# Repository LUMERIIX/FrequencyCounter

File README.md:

# FrequencyCounter - The most powerfull DIY FrequnecyCounter
## Introduction
FrequencyCounter is a soft- and hardware project which is a FPGA based FrequencyCounter. The FrequencyCounter is controlled by an GUI Interface ([SigrokLcd](https://github.com/LUMERIIX/SigrokLcd) )on the usb connected Host-PC. A single USB cable for Data and Power supply keeps the construction simple and clean as possible. The GUI is custom-made for this project behind the GUI runs [Sigrok](https://sigrok.org/) a open-source tool for controlling measure devices like frequency counters, multimeters, oscilloscopes etc. The project aims to be a simple, cheap, useful and accurate measure device for everyone. The layout is made in [KiCad]( http://kicad.org/) a open-source layout tool. The Project is open and everyone is wellcome to work on this project and contribute his extensions and improvements.

## Concept
Comming Soon!

## Hardware
The Hardware is based on a Spartan 6 FPGA which is the heartpiece of the entire circuit. The circuit is reduced to its minimal. The PCB ist a four-layer 1.6mm thick FR4 Board which makes it more expensive but the layout is much cleaner and the signal quality can be increased. The PCB has mounted components on top and bottom site of it. The Mounting on the bottom site is reduced to the minimal to keep it simple an allows also the use without a hosing.<br> 

### Housing
I created a simple and clean plexiglas housing for the PCB which fits the style of the prject very well. The design of the housing is inspired by the [Sick of Beige](http://dangerousprototypes.com/docs/Sick_of_Beige_compatible_cases) cases.<br> 

### Internal Clock Reference
The mouting of the Circuit give you the choice to mout the expensive **OCXO**(Oven Controlled Oscillator) or the way cheaper **VCTCXO**(Voltage Controller Temperatur Compensated Oscillator). In fact of this the precicion of the tool is scalable but I recommend you to mount the cheaper option because the difference in the accuracy is not as much as the price difference. <br>

### Input Circuits
The Input Circuits of each channel are different because not one of them fit in all usage situations.<br> 
The input circuit of **CHA** is realized with an voltage limiter and a HP-Filter at the inlet, followed by a divider (/8) with a HP-Filter and a voltage divider at the output to change the bias point. The change of the bias point is neccessary for the fpga to allow the signal detection.<br>
The most complex incput circuit is the one of the **external reference** (Ext.Ref). The circuit is out of the LTC6957 Datasheet and is often used for reference clocks. The transformator at the inlet make it impossible to use this circuit for both other channels of the FrequencyCounter (frequnecy reasons).<br>
**Channel B** is simpler than the other input ciruits. After the inlet it follows a voltage limiter and a very-fast comparator for edge detecting.<br>
### Communication
The Communication of the Device is over USB/UART through this its possible to have only one cable for programming, powersupply and also communication. On the PCB of the Counter a FTDI (FT2232) is mounted. Through this chip it's possible to programm the FPGA with JTAG and also have a USART Bus to the FPGA for the communication and the data. The Protocol which is used for the controlling consits only out of one command-byte which controls the hole device. The Commands you see in the Command Overview.<br>
**Command Overview**<br><br>
<br><br>
**Communication Overview**<br><br>
<br>

### Hardware Overview:<br>
<br>

## Software
### VHDL
**UART**<br>
The UART component isn't self written it is a adjusted version of the [UART component of Scott Larson](https://eewiki.net/pages/viewpage.action?pageId=59507062) of the eewiki. The component was extended by a Wishbone Interface to fit the projects architecture. The UART interface is used for the communication with the host-pc.<br><br>
**I2C**<br>
The I2C Master Component is also not self written it's base is from [opencores](https://opencores.org/project,i2c?do=projects&download=i2c). The component works fine and it's a big advantage to have a originally wishbone interface included. I2C is in the FrequnecyCounter used to control the DAC wich provides to control voltage for the oscillators.<br><br>
**ZPU**<br>
The [ZPU](https://github.com/zylin/zpu) is a open-source VHDL project from github wich includes a small 32bit CPU. The base ZPU Repo consist of different cores and testbenches but is very confusing. In fact of this I created a fork of the repo and set up a [working base](https://github.com/LUMERIIX/zpu) for the FrequencyCounter Project.<br><br>
**FrequencyCounter**<br>
The FrequencyCounter VHDL Code is the main part which counts our signals. The FrequencyCounter includes a ChannelSelctor which connect the desired Channels to the Counter itself. Furthermore the component includes a GateTimeGenerator which open a Countergate for a selected duration of time. The Signals are counted simultaneously with two identical VHDL counters. Each counter counts the amout of signal periods in this GateTime. Through the knowledge of the constant reference and the countervalue of the Reference Clock we can calculate the frequency of the unknown signal. This kind of Counter is called [Recirprocal Counter](https://en.wikipedia.org/wiki/Frequency_counter).<br><br>
**Procedure & Calculation**<br><br>
<br><br>

<br><br><br><br><br><br><br><br><br><br>

**VHDL Abstraction**<br><br>
<br><br>
**VHDL FrequencyCounter Abstraction**<br><br>
<br>
### C-Code
The C-Code is the Programm Code for the implemented VHDL CPU [ZPU](https://github.com/zylin/zpu) or a so called [SOC](https://en.wikipedia.org/wiki/System_on_a_chip)(System-on-a-Chip). The C-Code implements the Protocol for the communication over uart and i2c. The ZPU also controls the entire VHDL Components and handles the data. The Code is obviously written in C and is based on a state-machine. The C-Code is converted in a dualported-RAM (VHDL Component) which is located in the VHDL Project and is connected to the Wishbone-Bus of the ZPU. 

## Download & Installation
**It's recommended to use a Linux Host-PC the project is tested and developt on Fedora 27 so I recommend to install a Fedora VM in VMWare Worksation**

```
cd
gedit .bashrc
```
Add following lines:
```
export PKG_CONFIG_PATH=/usr/local/lib/pkgconfig/ 
export PYTHONPATH=/usr/local/lib64/python2.7/site-packages/
```
Save and Close gedit.<br>
Install dependencies:
```
sudo dnf install gcc-gfortran apr-devel apr-util-devel octave*
sudo dnf install gcc-c++
sudo dnf update
sudo dnf upgrade
sudo svn git cppunit-devel rabbitvcs*
sudo dnf copr enable jenslody/codeblocks
sudo dnf install codeblocks codeblocks-contrib
sudo dnf install libftdi-devel libusb-devel xterm
sudo dnf install automake libtool autoconf make cmake autoconf-archive pkgconfig glib2-devel libzip-devel check-devel doxygen
sudo dnf install glibmm24-devel python-devel numpy pygobject3-devel swig
sudo dnf install redhat-rpm-config python3-devel qt5 qt5-devel boost-devel
```
Next Install libserialport and the adjusted version of libsigrok:
```
git clone git://sigrok.org/libserialport
cd /libserialport
./autogen.sh 
./configure
make
sudo make install

git clone https://github.com/LUMERIIX/libsigrok_FreqCount
cd libsigrok_FreqCount
./autogen.sh
PKG_CONFIG_PATH=/usr/local/lib/pkgconfig/ ./configure 
make -j4
sudo PKG_CONFIG_PATH=/usr/local/lib/pkgconfig/ PYTHONPATH=/usr/local/lib64/python2.7/site-packages/ make install
sudo ldconfig /usr/local/lib
```
Download the FrequencyCounter Repo:
```
git clone https://github.com/LUMERIIX/FrequencyCounter
cd FrequencyCounter 
```
**Optional** Download the fork of the ZPU Repo to have all source files 
```
cd
git clone https://github.com/LUMERIIX/zpu
```
The source files are located under
```
cd zpu/zpu/hdl/zpu4
```
Next Install openocd for flashing the bitstream:
```
sudo dnf install git libtool autoconf texinfo libusb-dev
sudo dnf install libftdi
cd
git clone git://git.code.sf.net/p/openocd/code openocd
cd ~/openocd
./bootstrap
./configure --enable-maintainer-mode --disable-werror --enable-ftdi
make
sudo make install
```
Create Directory for Config files of Openocd
```
cd ~
mkdir openocd-bin
cd ~/openocd/tcl
cp -r * ~/openocd-bin
cd ../src
cp openocd ~/openocd-bin
```
Add the Interface Config file for the FT2232
```
cd 
cp FrequnecyCounter/FTDI/ft2232-jtag.cfg openocd-bin/interface/ftdi
```
Download [SigrokLcd](https://github.com/LUMERIIX/SigrokLcd) or [SigrokCLI](https://sigrok.org/wiki/Linux)

### Set up the FTDI Chip (FT2232d)
First download [FT_PROG](http://www.ftdichip.com/Support/Utilities.htm#FT_PROG) and install it on your Host-pc.<br>
Open FT_PROG and Load FrequencyCounter.xml Template from directrory /FrequnceyCounter/Documentation/FrequencyCounter_Template.xml<br>
Connect your FrequencyCounter via USB to the Host-PC and power it!<br>
**Check first the Voltages of the Powersupply on the PCB to make sure the circuit is working correctly!**<br>
Scan for Devices (Devices --> Scan&Parse)<br>
A Device with Chip Type: FT2232D should be listed in the Device Tree on the left.<br>
Program Template on FTDI Chip (Devices --> Program)<br>
Now your FTDI Chip should be set-up correctly
Else take a look in the [FT_PROG manual](http://www.ftdichip.com/Support/Documents/AppNotes/AN_124_User_Guide_For_FT_PROG.pdf)

## How to use it
The actual bitstream you find under /bitstream:
```
cd
cd FrequencyCounter/bitstream
```
To flash the bitstream move to the openocd directory
```
cd
cd openocd
mdkdir bitstream
cp ../FrequencyCounter/bitstream/frequencycountertop.bit bitstream
```
Flash Command
```
openocd -f interface/ftdi/ft2232-jtag.cfg -f cpld/xilinx-xc6s.cfg -c "init; xc6s_program xc6s.tap; pld load 0 bitstream/frequnecycountertop.bit; exit"
```
**If a error is thrown try it as root.
And change write permission of the USB port where the Hardware is connected and try again!**

Open SigrokLcd and try to get some Data
```
cd
cd SigrokLcd/bin/Release
./SigrokLcd
```
If the GUI doesn't exit and you can finish the configuration of the connection in SigrokLcd you handled the bigest step. 
The Preset for the ChannelSelect is on CHA so you should receive a Frequency of quite a feq MHz. This Frequency exists through the output voltage swing of the frequency divider.<br>
**Congrats it seems that your DIY FrequencyCounter works!**

### Contact
If you have a Problem, a improvment or need Information don't hesitate to contact me.<br>
email: lukas.jenni@hotmail.de

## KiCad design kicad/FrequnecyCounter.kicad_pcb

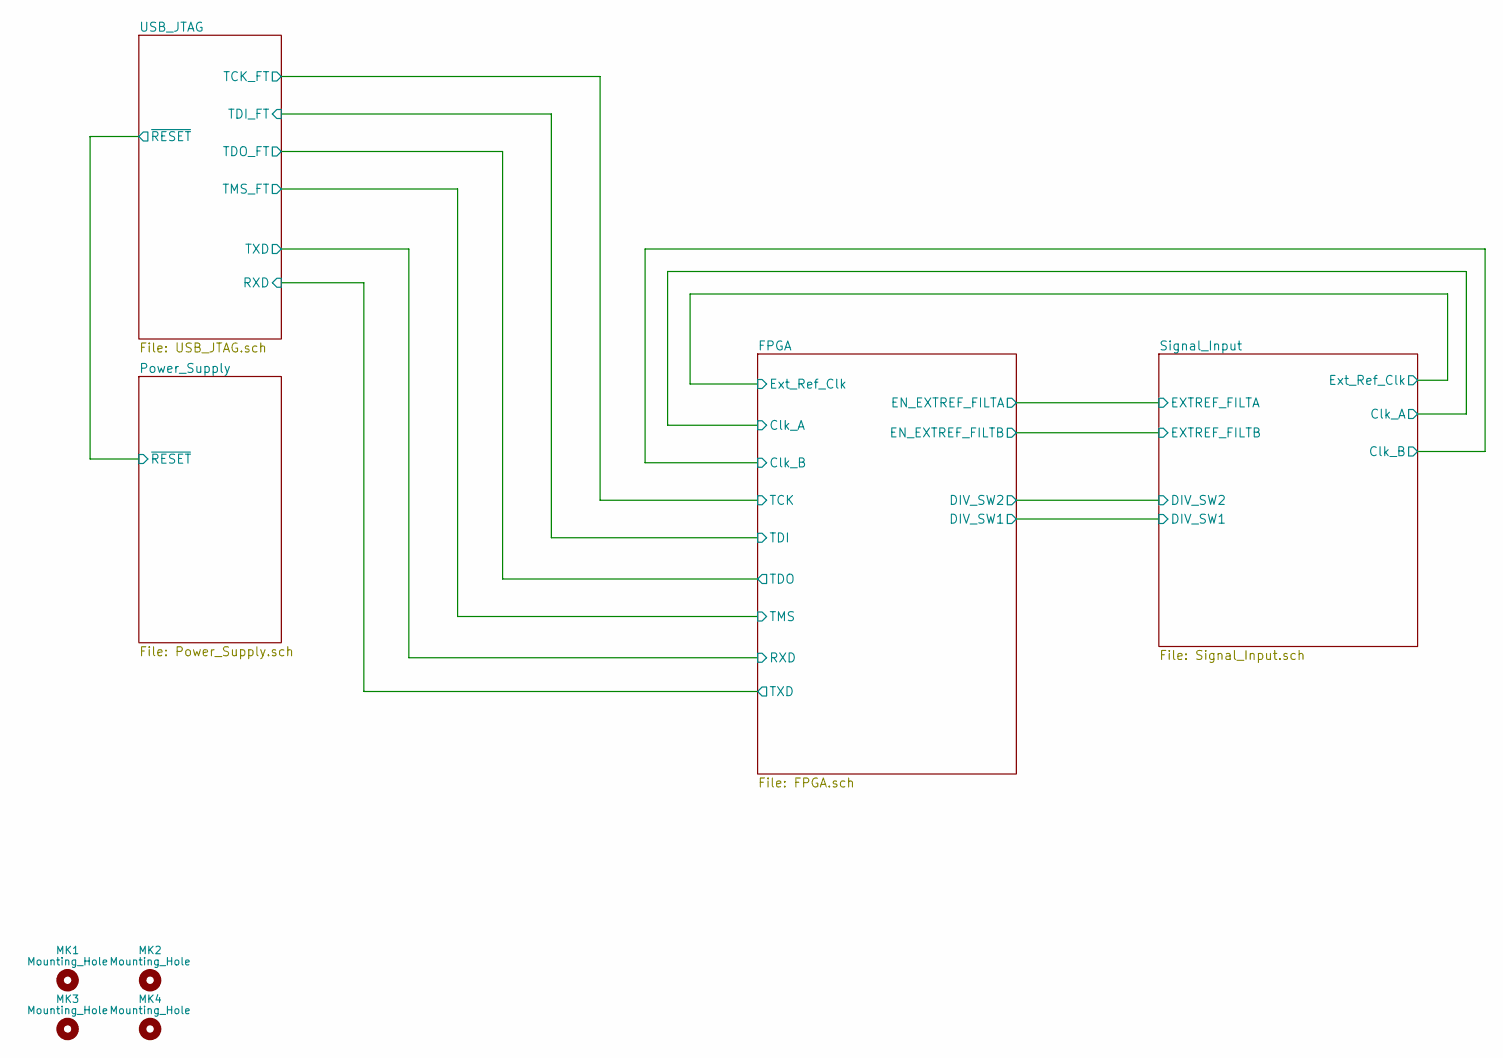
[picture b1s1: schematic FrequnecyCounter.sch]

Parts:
MK1, MK2, MK3, MK4: Mounting_Hole; MountingHole_3.2mm_M3_ISO7380

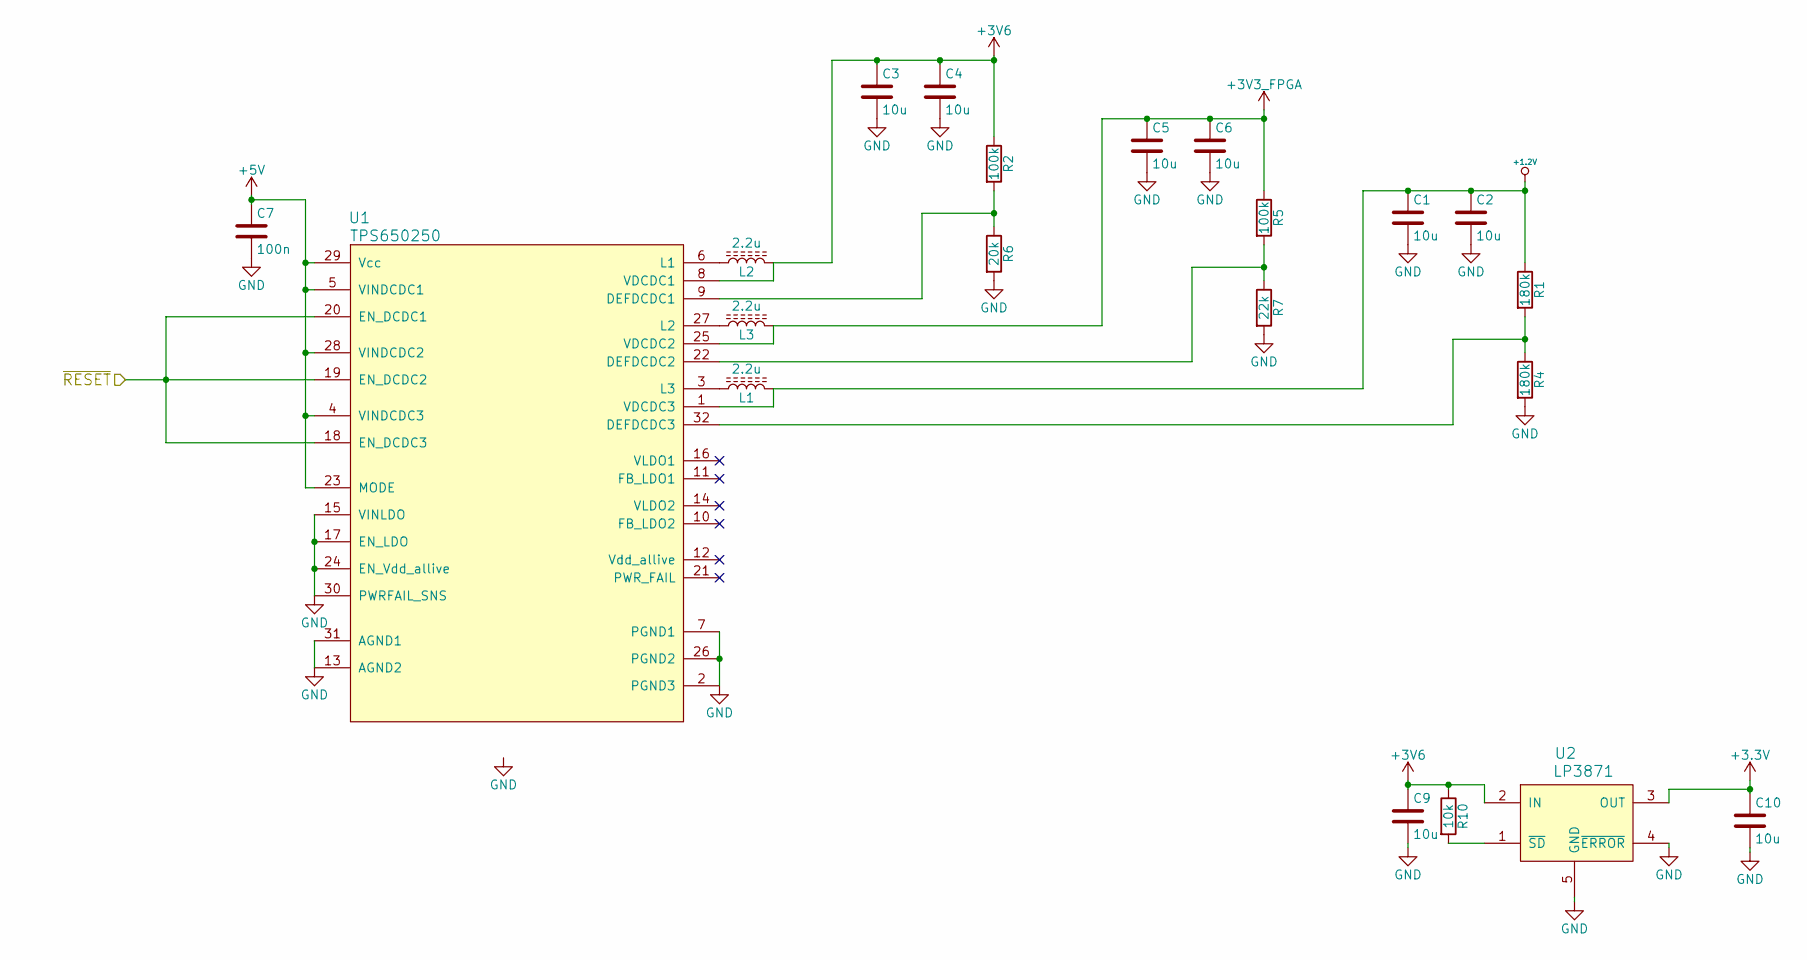
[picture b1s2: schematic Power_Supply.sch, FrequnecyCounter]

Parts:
C1, C2, C3, C4, C5, C6, C9, C10: 10u; Cap_0603_HandSoldering_1
C7: 100n; Cap_0603_HandSoldering_1
L1, L2, L3: 2.2u; LPS5030
R1, R4: 180k; R_0603_HandSoldering
R2, R5: 100k; R_0603_HandSoldering
R6: 20k; R_0603_HandSoldering
R7: 22k; R_0603_HandSoldering
R10: 10k; R_0603_HandSoldering
U1: TPS650250; QFN-32-1EP_5x5mm_Pitch0.5mm
U2: LP3871; SOT-223-5

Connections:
+1.2V: C1.1, C2.1, L1.2, R1.1, U1.1 (VDCDC3); also elsewhere on the board
+3V3_FPGA: C5.1, C6.1, L3.2, R5.1, U1.25 (VDCDC2); also elsewhere on the board
+3V6: C3.1, C4.1, C9.1, L2.2, R2.1, R10.1, U1.8 (VDCDC1), U2.2 (IN)
+5V: C7.1, U1.4 (VINDCDC3), U1.5 (VINDCDC1), U1.23 (MODE), U1.28 (VINDCDC2), U1.29 (Vcc); also elsewhere on the board
/Power_Supply/~RESET: U1.18 (EN_DCDC3), U1.19 (EN_DCDC2), U1.20 (EN_DCDC1); also elsewhere on the board
GND: C1.2, C2.2, C3.2, C4.2, C5.2, C6.2, C7.2, C9.2, C10.2, R4.2, R6.2, R7.2, U1.2 (PGND3), U1.7 (PGND1), U1.13 (AGND2), U1.15 (VINLDO), U1.17 (EN_LDO), U1.24 (EN_Vdd_allive), U1.26 (PGND2), U1.30 (PWRFAIL_SNS), U1.31 (AGND1), U1.33 (GND_PANEL), U2.4 (~ERROR), U2.5 (GND); also elsewhere on the board
unnamed: L1.1, U1.3 (L3)
unnamed: L2.1, U1.6 (L1)
unnamed: L3.1, U1.27 (L2)
unnamed: R1.2, R4.1, U1.32 (DEFDCDC3)
unnamed: R2.2, R6.1, U1.9 (DEFDCDC1)
unnamed: R5.2, R7.1, U1.22 (DEFDCDC2)
unnamed: R10.2, U2.1 (~SD)

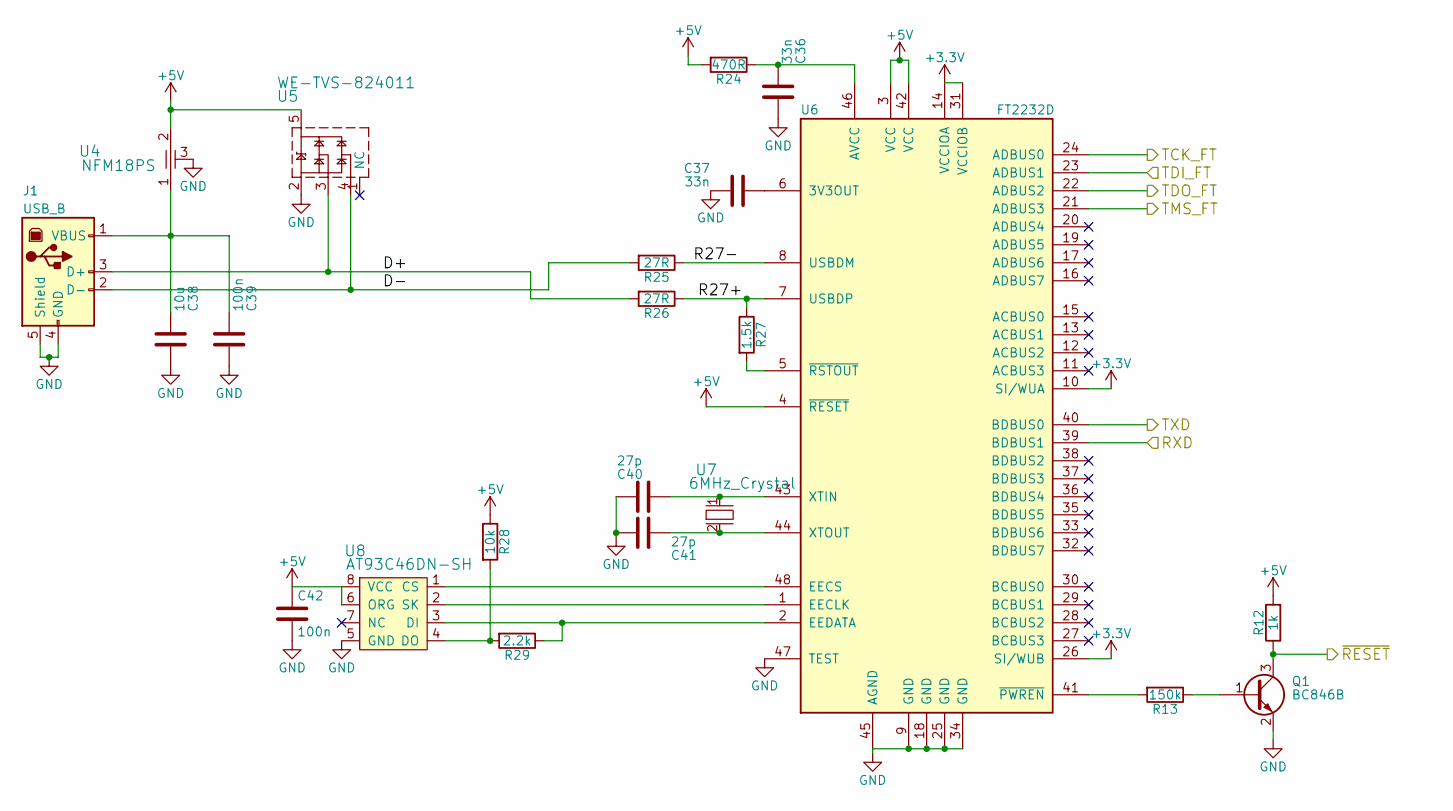
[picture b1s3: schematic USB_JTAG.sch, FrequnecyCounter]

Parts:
C36, C37: 33n; Cap_0603_HandSoldering_1
C38: 10u; Cap_0603_HandSoldering_1
C39, C42: 100n; Cap_0603_HandSoldering_1
C40, C41: 27p; Cap_0603_HandSoldering_1
J1: USB_B; USB_B_liegen_SMD
Q1: BC846B; SOT-23
R12: 1k; R_0603_HandSoldering
R13: 150k; R_0603_HandSoldering
R24: 470R; R_0603_HandSoldering
R25, R26: 27R; R_0603_HandSoldering
R27: 1.5k; R_0603_HandSoldering
R28: 10k; R_0603_HandSoldering
R29: 2.2k; R_0603_HandSoldering
U4: NFM18PS
U5: WE-TVS-824011; SOT-23-5
U6: FT2232D; LQFP-48_7x7mm_Pitch0.5mm
U7: 6MHz_Crystal; Crystal_SMD_HC49-SD
U8: AT93C46DN-SH; SOIC-8_3.9x4.9mm_Pitch1.27mm

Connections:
+5V: C42.1, R12.2, R24.2, R28.1, U4.2, U5.5, U6.3 (VCC), U6.4 (~RESET), U6.42 (VCC), U8.6 (ORG), U8.8 (VCC); also elsewhere on the board
/FPGA/RXD: U6.40 (BDBUS0); also elsewhere on the board
/FPGA/TCK: U6.24 (ADBUS0); also elsewhere on the board
/FPGA/TDI: U6.23 (ADBUS1); also elsewhere on the board
/FPGA/TDO: U6.22 (ADBUS2); also elsewhere on the board
/FPGA/TMS: U6.21 (ADBUS3); also elsewhere on the board
/Power_Supply/~RESET: Q1.3 (C), R12.1; also elsewhere on the board
/USB_JTAG/D+: J1.3 (D+), R26.2, U5.3
/USB_JTAG/D-: J1.2 (D-), R25.2, U5.4
/USB_JTAG/R27+: R26.1, R27.1, U6.7 (USBDP)
/USB_JTAG/R27-: R25.1, U6.8 (USBDM)
/USB_JTAG/RXD: U6.39 (BDBUS1); also elsewhere on the board
GND: C36.2, C37.1, C38.2, C39.2, C40.2, C41.2, C42.2, J1.4 (GND), J1.5 (Shield), Q1.2 (E), U4.3, U5.2, U6.9 (GND), U6.18 (GND), U6.25 (GND), U6.34 (GND), U6.45 (AGND), U6.47 (TEST), U8.5 (GND); also elsewhere on the board
unnamed: C36.1, R24.1, U6.46 (AVCC)
unnamed: C37.2, U6.6 (3V3OUT)
unnamed: C38.1, C39.1, J1.1 (VBUS), U4.1
unnamed: C40.1, U6.43 (XTIN), U7.1
unnamed: C41.1, U6.44 (XTOUT), U7.2
unnamed: Q1.1 (B), R13.1
unnamed: R13.2, U6.41 (~PWREN)
unnamed: R27.2, U6.5 (~RSTOUT)
unnamed: R28.2, R29.2, U8.4 (DO)
unnamed: R29.1, U6.2 (EEDATA), U8.3 (DI)
unnamed: U6.1 (EECLK), U8.2 (SK)
unnamed: U6.48 (EECS), U8.1 (CS)

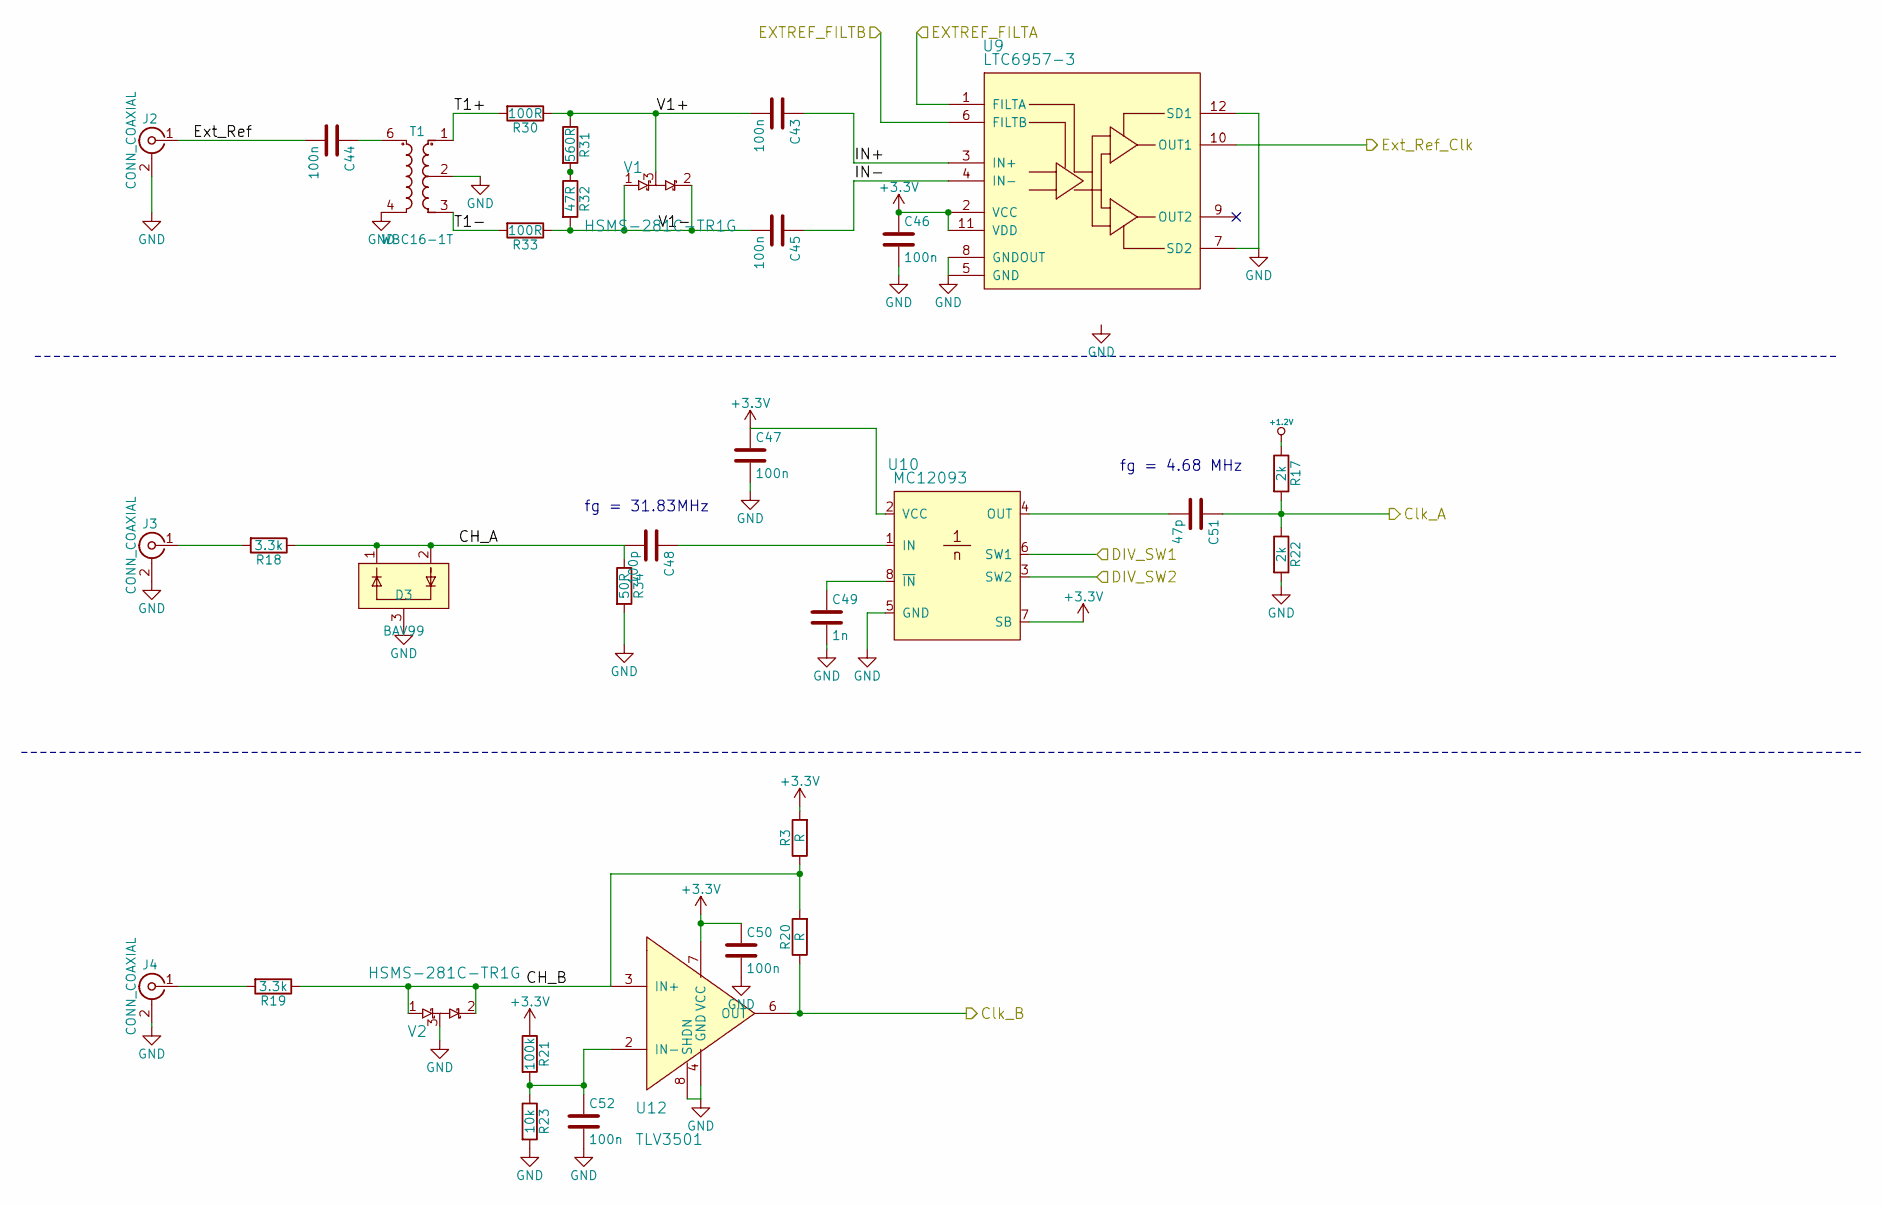
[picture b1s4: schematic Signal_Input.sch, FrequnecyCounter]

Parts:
C43, C44, C45, C46, C47, C50, C52: 100n; Cap_0603_HandSoldering_1
C48: 100p; Cap_0603_HandSoldering_1
C49: 1n; Cap_0603_HandSoldering_1
C51: 47p; Cap_0603_HandSoldering_1
D3: BAV99; SOT-23
J2, J3, J4: CONN_COAXIAL; bncf-horizontal
R3, R20: R; R_0603_HandSoldering
R17, R22: 2k; R_0603_HandSoldering
R18, R19: 3.3k; R_0603_HandSoldering
R21: 100k; R_0603_HandSoldering
R23: 10k; R_0603_HandSoldering
R30, R33: 100R; R_0603_HandSoldering
R31: 560R; R_0603_HandSoldering
R32: 47R; R_0603_HandSoldering
R34: 50R; R_0603_HandSoldering
T1: WBC16-1T; wbc-16-1T
U9: LTC6957-3; DFN-12-1EP_3x3mm_Pitch0.45mm
U10: MC12093; SOIC-8_3.9x4.9mm_Pitch1.27mm
U12: TLV3501; SOIC-8-N
V1, V2: HSMS-281C-TR1G; SOT-323_SC-70_Handsoldering

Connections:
+1.2V: R17.1; also elsewhere on the board
/FPGA/Clk_A: C51.1, R17.2, R22.1; also elsewhere on the board
/FPGA/Clk_B: R20.1, U12.6 (OUT); also elsewhere on the board
/FPGA/DIV_SW1: U10.6 (SW1); also elsewhere on the board
/FPGA/DIV_SW2: U10.3 (SW2); also elsewhere on the board
/FPGA/EN_EXTREF_FILTA: U9.1 (FILTA); also elsewhere on the board
/FPGA/EN_EXTREF_FILTB: U9.6 (FILTB); also elsewhere on the board
/FPGA/Ext_Ref_Clk: U9.10 (OUT1); also elsewhere on the board
/Signal_Input/CH_A: C48.2, D3.1, D3.2, R18.1, R34.1
/Signal_Input/CH_B: R3.1, R19.1, R20.2, U12.3 (IN+), V2.1, V2.2
/Signal_Input/Ext_Ref: C44.2, J2.1 (In)
/Signal_Input/IN+: C43.1, U9.3 (IN+)
/Signal_Input/IN-: C45.1, U9.4 (IN-)
/Signal_Input/T1+: R30.2, T1.1
/Signal_Input/T1-: R33.2, T1.3
/Signal_Input/V1+: C43.2, R30.1, R31.1, V1.3
/Signal_Input/V1-: C45.2, R32.2, R33.1, V1.1, V1.2
GND: C46.2, C47.2, C49.2, C50.2, C52.2, D3.3, J2.2 (Ext), J3.2 (Ext), J4.2 (Ext), R22.2, R23.2, R34.2, T1.2, T1.4, U9.5 (GND), U9.7 (SD2), U9.8 (GNDOUT), U9.12 (SD1), U9.13 (GND_Panel), U10.5 (GND), U12.4 (GND), U12.8 (SHDN), V2.3; also elsewhere on the board
unnamed: C44.1, T1.6
unnamed: C48.1, U10.1 (IN)
unnamed: C49.1, U10.8 (~IN)
unnamed: C51.2, U10.4 (OUT)
unnamed: C52.1, R21.2, R23.1, U12.2 (IN-)
unnamed: J3.1 (In), R18.2
unnamed: J4.1 (In), R19.2
unnamed: R31.2, R32.1

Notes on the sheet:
fg = 4.68 MHz
fg = 31.83MHz

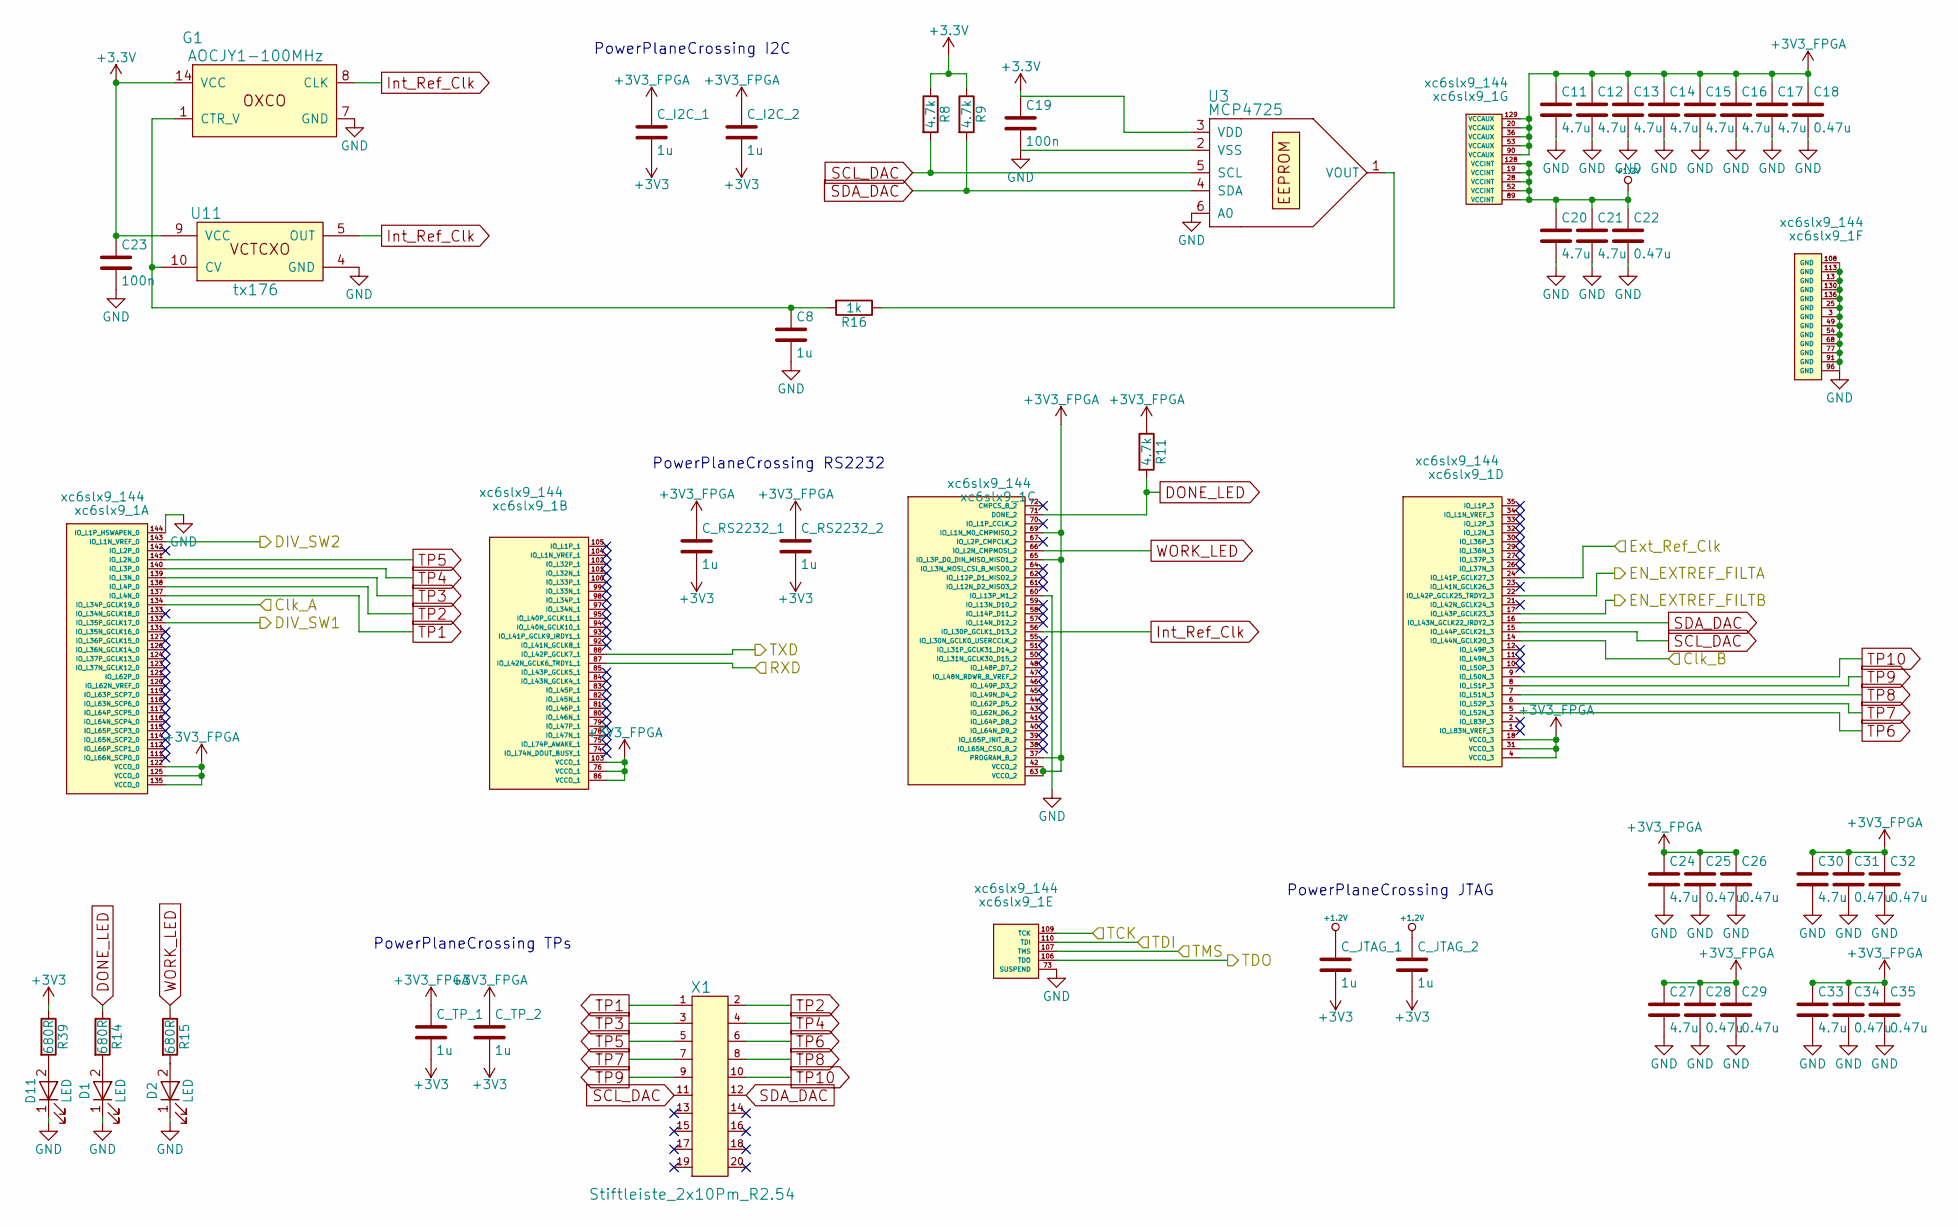
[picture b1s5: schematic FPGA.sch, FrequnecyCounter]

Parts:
C8: 1u; Cap_0603_HandSoldering_1
C11, C12, C13, C14, C15, C16, C17, C20, C21, C24, C27, C30, C33: 4.7u; Cap_0603_HandSoldering_1
C18, C22, C25, C26, C28, C29, C31, C32, C34, C35: 0.47u; Cap_0603_HandSoldering_1
C19, C23: 100n; Cap_0603_HandSoldering_1
C_I2C_1, C_I2C_2: 1u; Cap_0603_HandSoldering_1
C_JTAG_1, C_JTAG_2: 1u; Cap_0603_HandSoldering_1
C_RS2232_1, C_RS2232_2: 1u; Cap_0603_HandSoldering_1
C_TP_1, C_TP_2: 1u; Cap_0603_HandSoldering_1
D1, D2, D11: LED; Mini_TopLed_SMD
G1: AOCJY1-100MHz; Crystal_smd_4pin_20.8x13.2
R8, R9, R11: 4.7k; R_0603_HandSoldering
R14, R15, R39: 680R; R_0603_HandSoldering
R16: 1k; R_0603_HandSoldering
U3: MCP4725; SOT-23-6_Handsoldering
U11: tx176
X1: Stiftleiste_2x10Pm_R2.54
xc6slx9_1: xc6slx9_144; TQFP-144_20x20mm_Pitch0.5mm

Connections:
+1.2V: C20.1, C21.1, C22.1, C_JTAG_1.1, C_JTAG_2.1, xc6slx9_1.19 (VCCINT), xc6slx9_1.28 (VCCINT), xc6slx9_1.52 (VCCINT), xc6slx9_1.89 (VCCINT), xc6slx9_1.128 (VCCINT); also elsewhere on the board
+3V3_FPGA: C11.1, C12.1, C13.1, C14.1, C15.1, C16.1, C17.1, C18.1, C24.1, C25.1, C26.1, C27.1, C28.1, C29.1, C30.1, C31.1, C32.1, C33.1, C34.1, C35.1, C_I2C_1.1, C_I2C_2.1, C_RS2232_1.1, C_RS2232_2.1, C_TP_1.1, C_TP_2.1, R11.1, xc6slx9_1.4 (VCCO_3), xc6slx9_1.18 (VCCO_3), xc6slx9_1.20 (VCCAUX), xc6slx9_1.31 (VCCO_3), xc6slx9_1.36 (VCCAUX), xc6slx9_1.37 (PROGRAM_B_2), xc6slx9_1.42 (VCCO_2), xc6slx9_1.53 (VCCAUX), xc6slx9_1.63 (VCCO_2), xc6slx9_1.65 (IO_L3P_D0_DIN_MISO_MISO1_2), xc6slx9_1.69 (IO_L1N_M0_CMPMISO_2), xc6slx9_1.76 (VCCO_1), xc6slx9_1.86 (VCCO_1), xc6slx9_1.90 (VCCAUX), xc6slx9_1.103 (VCCO_1), xc6slx9_1.122 (VCCO_0), xc6slx9_1.125 (VCCO_0), xc6slx9_1.129 (VCCAUX), xc6slx9_1.135 (VCCO_0); also elsewhere on the board
/FPGA/Clk_A: xc6slx9_1.134 (IO_L34P_GCLK19_0); also elsewhere on the board
/FPGA/Clk_B: xc6slx9_1.14 (IO_L44N_GCLK20_3); also elsewhere on the board
/FPGA/DIV_SW1: xc6slx9_1.132 (IO_L35P_GCLK17_0); also elsewhere on the board
/FPGA/DIV_SW2: xc6slx9_1.143 (IO_L1N_VREF_0); also elsewhere on the board
/FPGA/EN_EXTREF_FILTA: xc6slx9_1.22 (IO_L42P_GCLK25_TRDY2_3); also elsewhere on the board
/FPGA/EN_EXTREF_FILTB: xc6slx9_1.17 (IO_L43P_GCLK23_3); also elsewhere on the board
/FPGA/Ext_Ref_Clk: xc6slx9_1.24 (IO_L41P_GCLK27_3); also elsewhere on the board
/FPGA/RXD: xc6slx9_1.87 (IO_L42N_GCLK6_TRDY1_1); also elsewhere on the board
/FPGA/TCK: xc6slx9_1.109 (TCK); also elsewhere on the board
/FPGA/TDI: xc6slx9_1.110 (TDI); also elsewhere on the board
/FPGA/TDO: xc6slx9_1.106 (TDO); also elsewhere on the board
/FPGA/TMS: xc6slx9_1.107 (TMS); also elsewhere on the board
/USB_JTAG/RXD: xc6slx9_1.88 (IO_L42P_GCLK7_1); also elsewhere on the board
DONE_LED: R11.2, R14.1, xc6slx9_1.71 (DONE_2)
GND: C8.2, C11.2, C12.2, C13.2, C14.2, C15.2, C16.2, C17.2, C18.2, C19.2, C20.2, C21.2, C22.2, C23.2, C24.2, C25.2, C26.2, C27.2, C28.2, C29.2, C30.2, C31.2, C32.2, C33.2, C34.2, C35.2, D1.1 (K), D2.1 (K), D11.1 (K), G1.7 (GND), U3.2 (VSS), U3.6 (A0), U11.4 (GND), xc6slx9_1.3 (GND), xc6slx9_1.13 (GND), xc6slx9_1.25 (GND), xc6slx9_1.49 (GND), xc6slx9_1.54 (GND), xc6slx9_1.60 (IO_L13P_M1_2), xc6slx9_1.68 (GND), xc6slx9_1.73 (SUSPEND), xc6slx9_1.77 (GND), xc6slx9_1.91 (GND), xc6slx9_1.96 (GND), xc6slx9_1.108 (GND), xc6slx9_1.113 (GND), xc6slx9_1.130 (GND), xc6slx9_1.136 (GND), xc6slx9_1.144 (IO_L1P_HSWAPEN_0); also elsewhere on the board
Int_Ref_Clk: G1.8 (CLK), U11.5 (OUT~), xc6slx9_1.56 (IO_L30P_GCLK1_D13_2)
unnamed: C8.1, G1.1 (CTR_V), R16.2, U11.10 (CV)
unnamed: D1.2 (A), R14.2
unnamed: D2.2 (A), R15.2
unnamed: D11.2 (A), R39.2
unnamed: R16.1, U3.1 (VOUT)
SCL_DAC: R8.2, U3.5 (SCL), X1.11, xc6slx9_1.15 (IO_L44P_GCLK21_3)
SDA_DAC: R9.2, U3.4 (SDA), X1.12, xc6slx9_1.16 (IO_L43N_GCLK22_IRDY2_3)
TP1: X1.1, xc6slx9_1.137 (IO_L4N_0)
TP2: X1.2, xc6slx9_1.138 (IO_L4P_0)
TP3: X1.3, xc6slx9_1.139 (IO_L3N_0)
TP4: X1.4, xc6slx9_1.140 (IO_L3P_0)
TP5: X1.5, xc6slx9_1.141 (IO_L2N_0)
TP6: X1.6, xc6slx9_1.5 (IO_L52N_3)
TP7: X1.7, xc6slx9_1.6 (IO_L52P_3)
TP8: X1.8, xc6slx9_1.7 (IO_L51N_3)
TP9: X1.9, xc6slx9_1.8 (IO_L51P_3)
TP10: X1.10, xc6slx9_1.9 (IO_L50N_3)
WORK_LED: R15.1, xc6slx9_1.66 (IO_L2N_CMPMOSI_2)

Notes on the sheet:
PowerPlaneCrossing TPs
PowerPlaneCrossing JTAG
PowerPlaneCrossing I2C
PowerPlaneCrossing RS2232

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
